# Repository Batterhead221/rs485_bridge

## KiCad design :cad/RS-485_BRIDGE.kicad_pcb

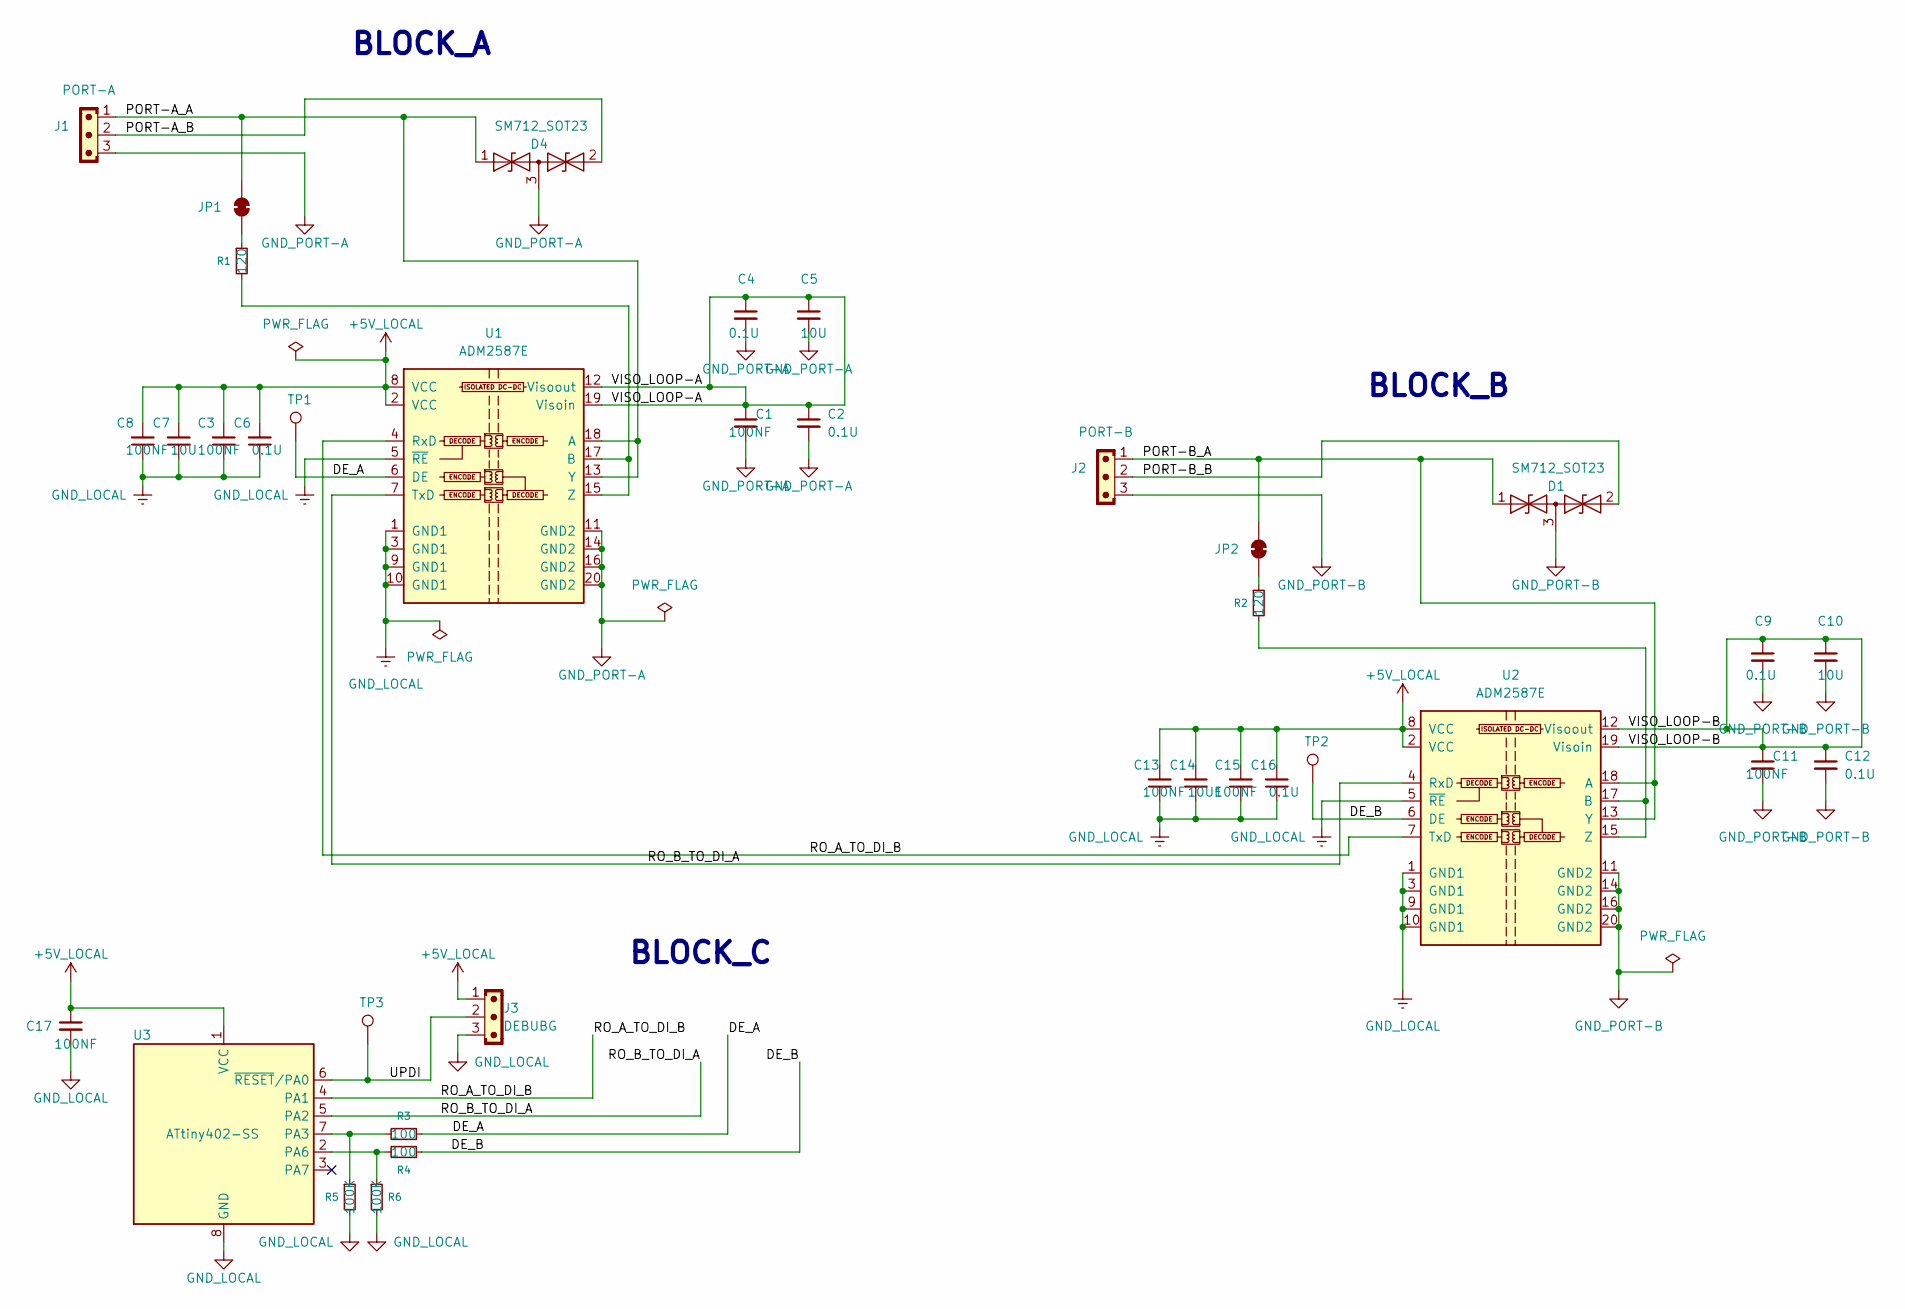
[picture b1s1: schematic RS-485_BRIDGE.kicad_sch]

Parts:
C1, C3, C8, C11, C13, C15, C17: 100NF; CAP 0402
C2, C12, C16: 0.1U; 1UF 0805
C4, C6, C9: 0.1U; CAP 0402
C5, C10: 10U; 1UF 0805
C7: 10U; CAP 0402
C14: 10UF; 1UF 0805
D1, D4: SM712_SOT23; SOT-23
J1: PORT-A; JST_PH_B3B-PH-K_1x03_P2.00mm_Vertical
J2: PORT-B; JST_PH_B3B-PH-K_1x03_P2.00mm_Vertical
J3: DEBUBG; SolderWire-1sqmm_1x03_P7.8mm_D1.4mm_OD3.9mm
JP1, JP2: SolderJumper_2_Bridged; SolderJumper-2_P1.3mm_Bridged_RoundedPad1.0x1.5mm
R1, R2: 120; R_0402_1005Metric_Pad0.72x0.64mm_HandSolder
R3, R4: 100; R_0402_1005Metric_Pad0.72x0.64mm_HandSolder
R5, R6: 100K; R_0402_1005Metric_Pad0.72x0.64mm_HandSolder
TP1, TP2: RE-A_N; TestPoint_Pad_D2.0mm
TP3: RE-A_N; TestPoint_Pad_1.0x1.0mm
U1, U2: ADM2587E; SOIC-20W_7.5x12.8mm_P1.27mm
U3: ATtiny402-SS; SOIC-8_3.9x4.9mm_P1.27mm

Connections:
+5V_LOCAL: C3.2, C6.2, C7.2, C8.2, C13.2, C14.2, C15.2, C16.2, C17.1, J3.1, U1.2 (VCC), U1.8 (VCC), U2.2 (VCC), U2.8 (VCC), U3.1 (VCC)
/DE_A: R3.1, TP1.1, U1.6 (DE)
/DE_B: R4.1, TP2.1, U2.6 (DE)
/PORT-A_A: D4.1 (A1), J1.1, JP1.2 (B), U1.13 (Y), U1.18 (A)
/PORT-A_B: D4.2 (A2), J1.2
/PORT-B_A: D1.1 (A1), J2.1, JP2.2 (B), U2.13 (Y), U2.18 (A)
/PORT-B_B: D1.2 (A2), J2.2
/RO_A_TO_DI_B: U1.4 (RxD), U2.7 (TxD), U3.4 (PA1)
/RO_B_TO_DI_A: U1.7 (TxD), U2.4 (RxD), U3.5 (PA2)
/UPDI: J3.2, TP3.1, U3.6 (~RESET/PA0)
/VISO_LOOP-A: C1.1, C2.1, C4.1, C5.1, U1.12 (Visoout), U1.19 (Visoin)
/VISO_LOOP-B: C9.1, C10.1, C11.1, C12.1, U2.12 (Visoout), U2.19 (Visoin)
GND_LOCAL: C3.1, C6.1, C7.1, C8.1, C13.1, C14.1, C15.1, C16.1, C17.2, J3.3, R5.2, R6.2, U1.1 (GND1), U1.3 (GND1), U1.5 (~RE), U1.9 (GND1), U1.10 (GND1), U2.1 (GND1), U2.3 (GND1), U2.5 (~RE), U2.9 (GND1), U2.10 (GND1), U3.8 (GND)
GND_PORT-A: C1.2, C2.2, C4.2, C5.2, D4.3 (common), J1.3, U1.11 (GND2), U1.14 (GND2), U1.16 (GND2), U1.20 (GND2)
GND_PORT-B: C9.2, C10.2, C11.2, C12.2, D1.3 (common), J2.3, U2.11 (GND2), U2.14 (GND2), U2.16 (GND2), U2.20 (GND2)
unnamed: JP1.1 (A), R1.1
unnamed: JP2.1 (A), R2.1
unnamed: R1.2, U1.15 (Z), U1.17 (B)
unnamed: R2.2, U2.15 (Z), U2.17 (B)
unnamed: R3.2, R5.1, U3.7 (PA3)
unnamed: R4.2, R6.1, U3.2 (PA6)

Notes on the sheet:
BLOCK_C
BLOCK_A
BLOCK_B

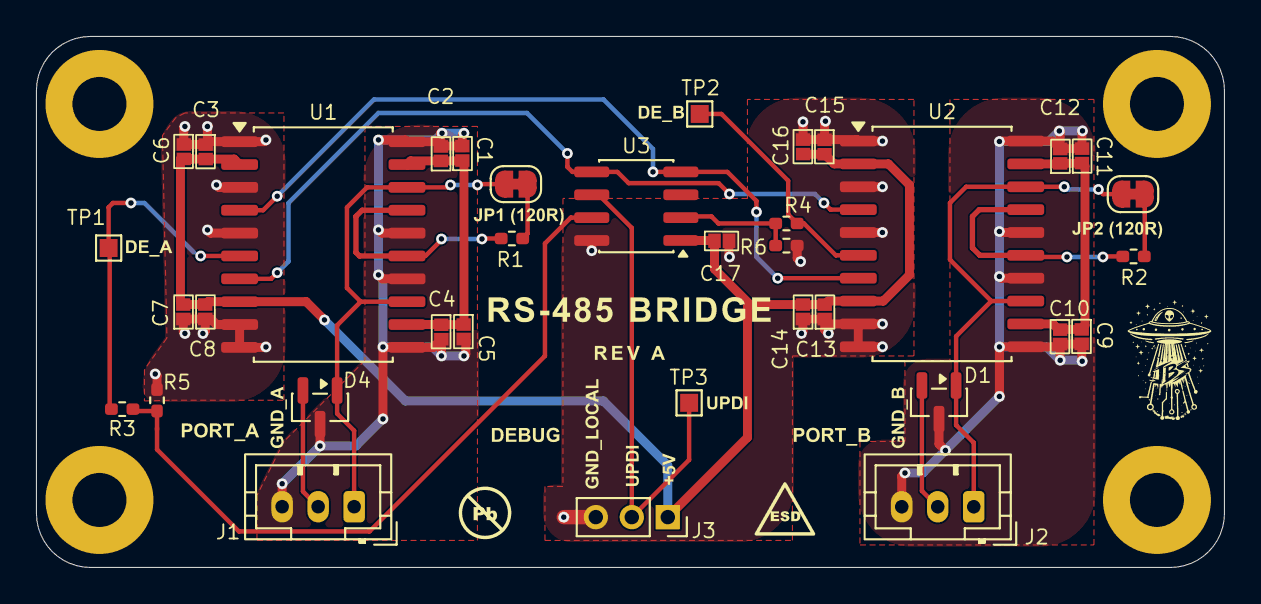
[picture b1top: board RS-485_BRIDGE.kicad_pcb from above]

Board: 2 copper layers, 66.0 x 29.5 mm, 36 parts (0 on the bottom side), 21 nets.

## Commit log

2026-04-18 file path restructure
2026-05-01 PICS
